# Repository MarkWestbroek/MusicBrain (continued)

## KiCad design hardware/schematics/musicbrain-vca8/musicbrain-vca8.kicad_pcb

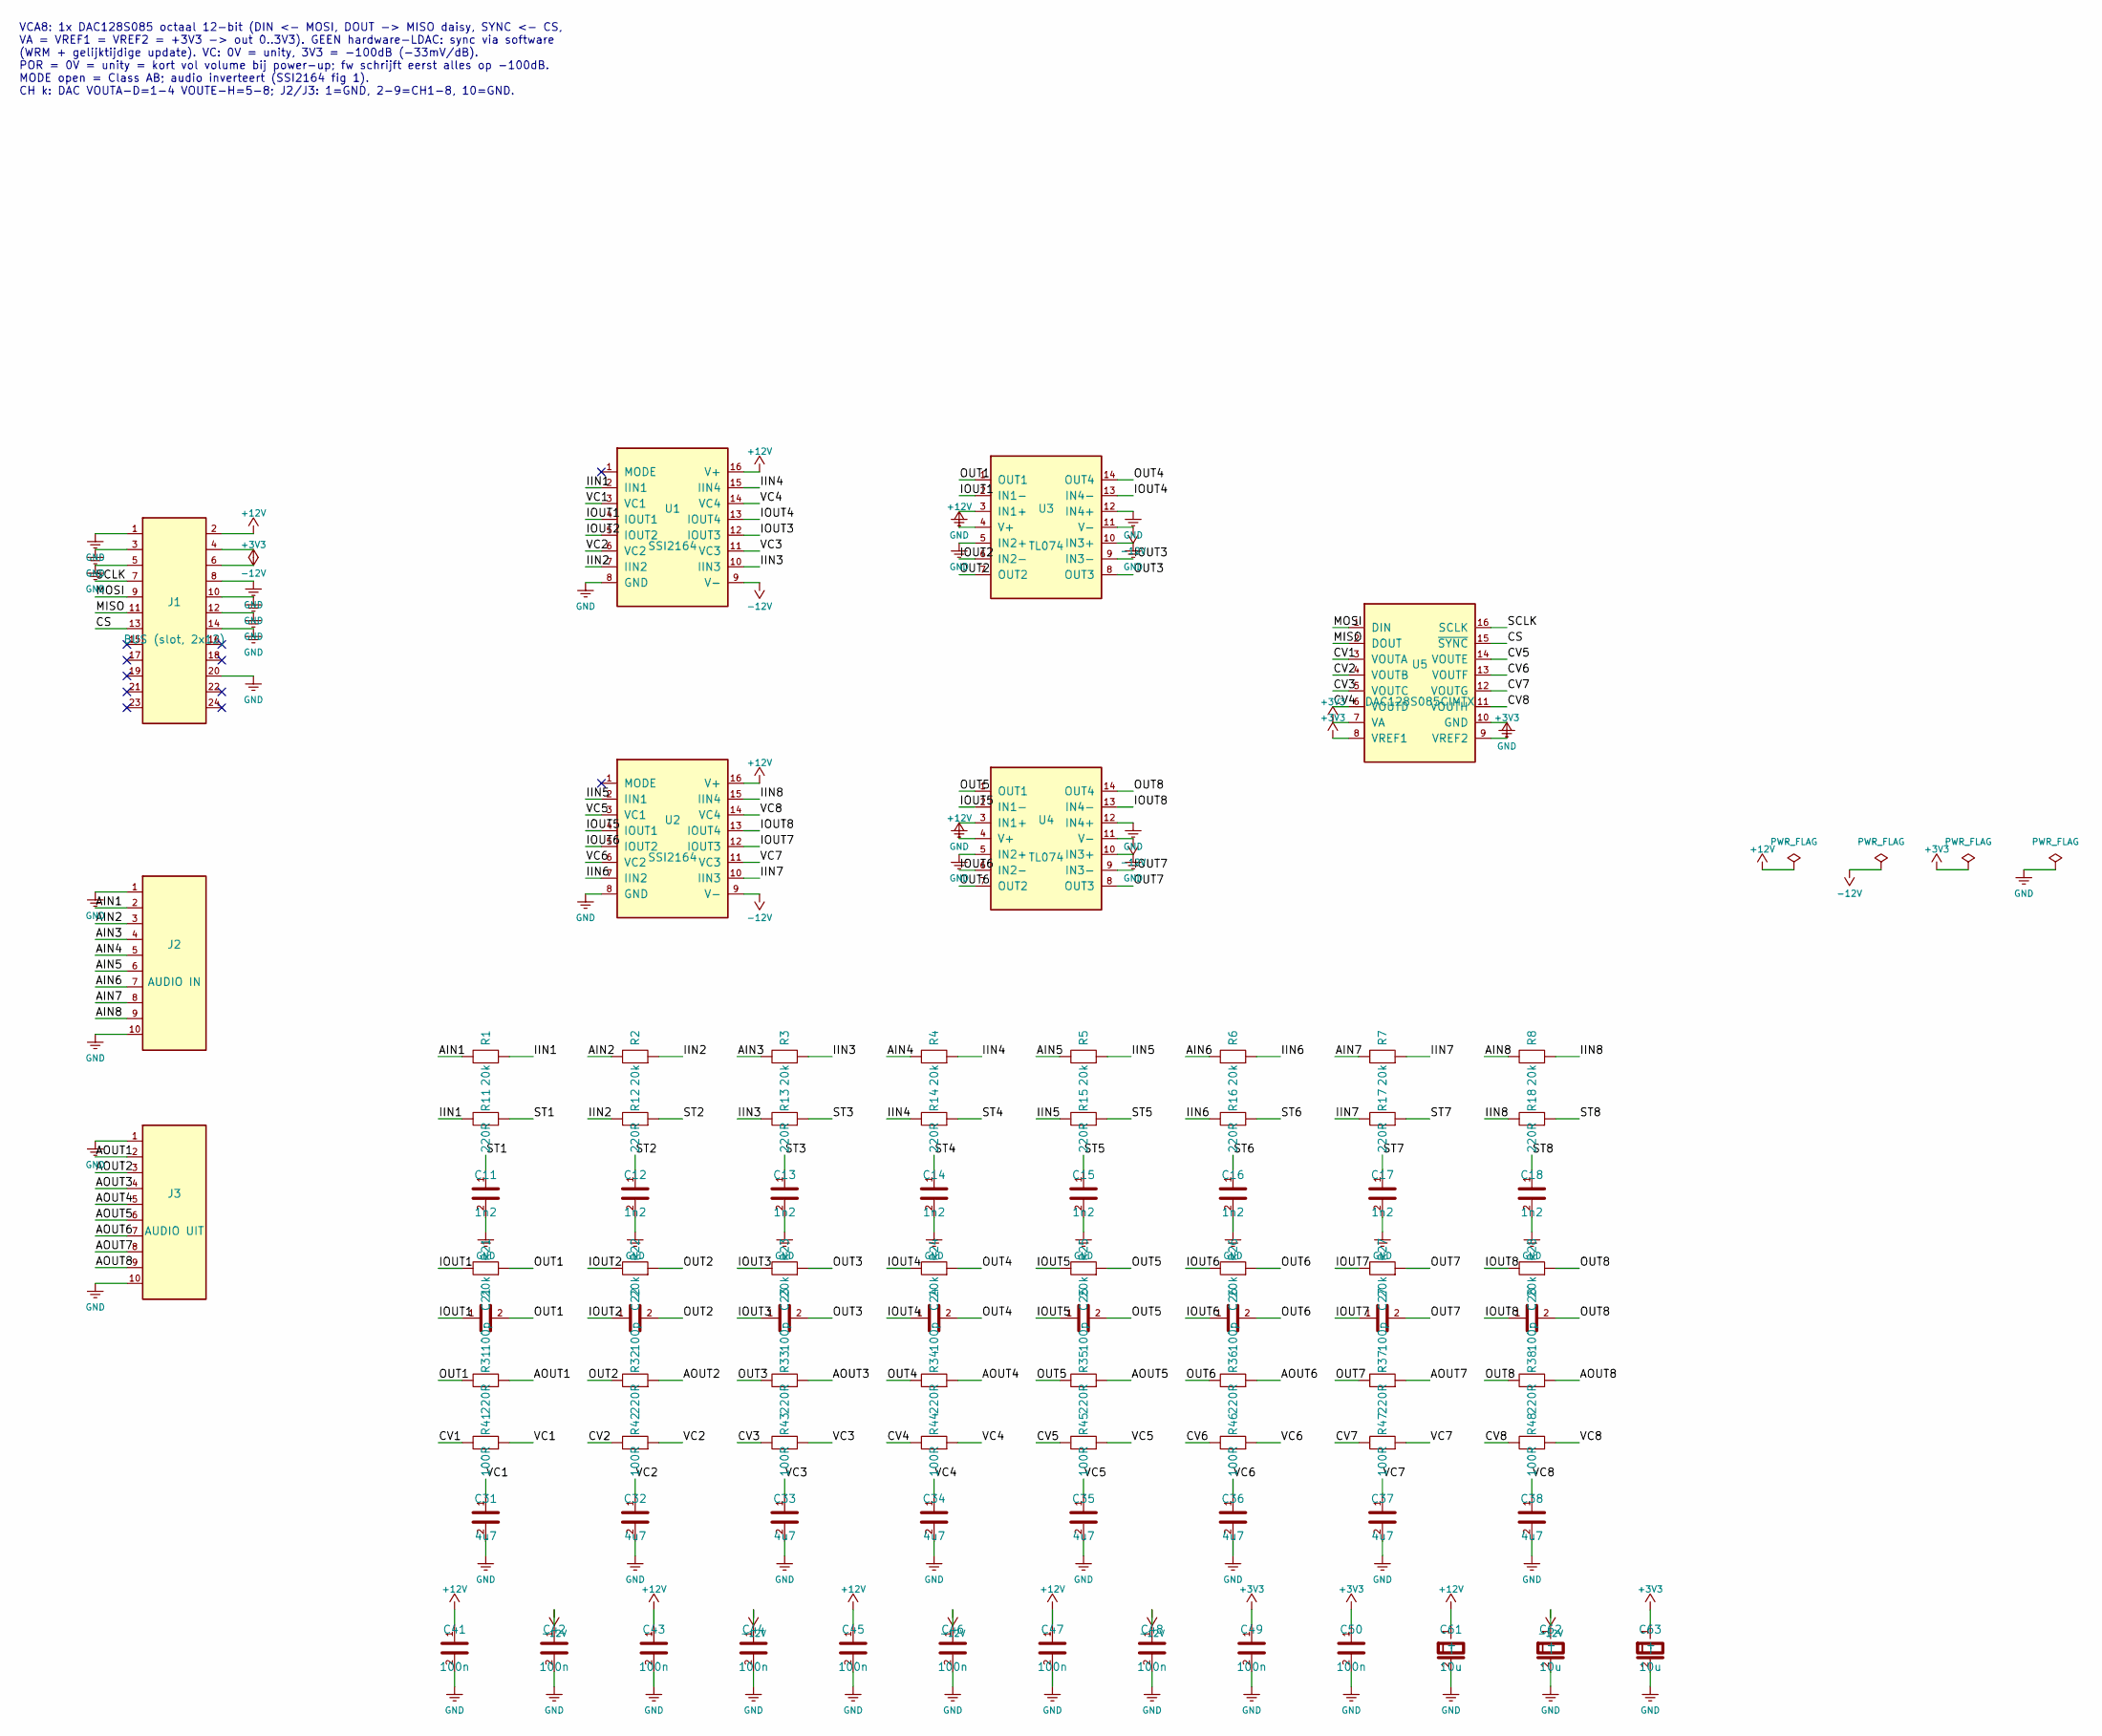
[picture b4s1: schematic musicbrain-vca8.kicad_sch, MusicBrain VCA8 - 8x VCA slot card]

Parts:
C11, C12, C13, C14, C15, C16, C17, C18: 1n2; C_0805_2012Metric
C21, C22, C23, C24, C25, C26, C27, C28: 100p; C_0805_2012Metric
C31, C32, C33, C34, C35, C36, C37, C38: 4u7; C_0805_2012Metric
C41, C42, C43, C44, C45, C46, C47, C48, C49, C50: 100n; C_0805_2012Metric
C61, C62, C63: 10u; CP_Elec_4x5.3
J1: BUS (slot, 2x12); PinHeader_2x12_P2.54mm_Horizontal
J2: AUDIO IN; PinHeader_1x10_P2.54mm_Horizontal
J3: AUDIO UIT; PinHeader_1x10_P2.54mm_Horizontal
R1, R2, R3, R4, R5, R6, R7, R8, R21, R22, R23, R24, R25, R26, R27, R28: 20k; R_0805_2012Metric
R11, R12, R13, R14, R15, R16, R17, R18, R31, R32, R33, R34, R35, R36, R37, R38: 220R; R_0805_2012Metric
R41, R42, R43, R44, R45, R46, R47, R48: 100R; R_0805_2012Metric
U1, U2: SSI2164; SOIC-16_3.9x9.9mm_P1.27mm
U3, U4: TL074; SOIC-14_3.9x8.7mm_P1.27mm
U5: DAC128S085CIMTX; TSSOP-16_4.4x5mm_P0.65mm

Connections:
+3V3: C49.1, C50.1, C63.1 (+), J1.6, U5.7 (VA), U5.8 (VREF1), U5.9 (VREF2)
+12V: C41.1, C43.1, C45.1, C47.1, C61.1 (+), J1.2, U1.16 (V+), U2.16 (V+), U3.4 (V+), U4.4 (V+)
-12V: C42.1, C44.1, C46.1, C48.1, C62.1 (+), J1.4, U1.9 (V-), U2.9 (V-), U3.11 (V-), U4.11 (V-)
/AIN1: J2.2, R1.1
/AIN2: J2.3, R2.1
/AIN3: J2.4, R3.1
/AIN4: J2.5, R4.1
/AIN5: J2.6, R5.1
/AIN6: J2.7, R6.1
/AIN7: J2.8, R7.1
/AIN8: J2.9, R8.1
/AOUT1: J3.2, R31.2
/AOUT2: J3.3, R32.2
/AOUT3: J3.4, R33.2
/AOUT4: J3.5, R34.2
/AOUT5: J3.6, R35.2
/AOUT6: J3.7, R36.2
/AOUT7: J3.8, R37.2
/AOUT8: J3.9, R38.2
/CS: J1.13, U5.15 (~SYNC)
/CV1: R41.1, U5.3 (VOUTA)
/CV2: R42.1, U5.4 (VOUTB)
/CV3: R43.1, U5.5 (VOUTC)
/CV4: R44.1, U5.6 (VOUTD)
/CV5: R45.1, U5.14 (VOUTE)
/CV6: R46.1, U5.13 (VOUTF)
/CV7: R47.1, U5.12 (VOUTG)
/CV8: R48.1, U5.11 (VOUTH)
/IIN1: R1.2, R11.1, U1.2 (IIN1)
/IIN2: R2.2, R12.1, U1.7 (IIN2)
/IIN3: R3.2, R13.1, U1.10 (IIN3)
/IIN4: R4.2, R14.1, U1.15 (IIN4)
/IIN5: R5.2, R15.1, U2.2 (IIN1)
/IIN6: R6.2, R16.1, U2.7 (IIN2)
/IIN7: R7.2, R17.1, U2.10 (IIN3)
/IIN8: R8.2, R18.1, U2.15 (IIN4)
/IOUT1: C21.1, R21.1, U1.4 (IOUT1), U3.2 (IN1-)
/IOUT2: C22.1, R22.1, U1.5 (IOUT2), U3.6 (IN2-)
/IOUT3: C23.1, R23.1, U1.12 (IOUT3), U3.9 (IN3-)
/IOUT4: C24.1, R24.1, U1.13 (IOUT4), U3.13 (IN4-)
/IOUT5: C25.1, R25.1, U2.4 (IOUT1), U4.2 (IN1-)
/IOUT6: C26.1, R26.1, U2.5 (IOUT2), U4.6 (IN2-)
/IOUT7: C27.1, R27.1, U2.12 (IOUT3), U4.9 (IN3-)
/IOUT8: C28.1, R28.1, U2.13 (IOUT4), U4.13 (IN4-)
/MISO: J1.11, U5.2 (DOUT)
/MOSI: J1.9, U5.1 (DIN)
/OUT1: C21.2, R21.2, R31.1, U3.1 (OUT1)
/OUT2: C22.2, R22.2, R32.1, U3.7 (OUT2)
/OUT3: C23.2, R23.2, R33.1, U3.8 (OUT3)
/OUT4: C24.2, R24.2, R34.1, U3.14 (OUT4)
/OUT5: C25.2, R25.2, R35.1, U4.1 (OUT1)
/OUT6: C26.2, R26.2, R36.1, U4.7 (OUT2)
/OUT7: C27.2, R27.2, R37.1, U4.8 (OUT3)
/OUT8: C28.2, R28.2, R38.1, U4.14 (OUT4)
/SCLK: J1.7, U5.16 (SCLK)
/ST1: C11.1, R11.2
/ST2: C12.1, R12.2
/ST3: C13.1, R13.2
/ST4: C14.1, R14.2
/ST5: C15.1, R15.2
/ST6: C16.1, R16.2
/ST7: C17.1, R17.2
/ST8: C18.1, R18.2
/VC1: C31.1, R41.2, U1.3 (VC1)
/VC2: C32.1, R42.2, U1.6 (VC2)
/VC3: C33.1, R43.2, U1.11 (VC3)
/VC4: C34.1, R44.2, U1.14 (VC4)
/VC5: C35.1, R45.2, U2.3 (VC1)
/VC6: C36.1, R46.2, U2.6 (VC2)
/VC7: C37.1, R47.2, U2.11 (VC3)
/VC8: C38.1, R48.2, U2.14 (VC4)
GND: C11.2, C12.2, C13.2, C14.2, C15.2, C16.2, C17.2, C18.2, C31.2, C32.2, C33.2, C34.2, C35.2, C36.2, C37.2, C38.2, C41.2, C42.2, C43.2, C44.2, C45.2, C46.2, C47.2, C48.2, C49.2, C50.2, C61.2 (-), C62.2 (-), C63.2 (-), J1.1, J1.3, J1.5, J1.8, J1.10, J1.12, J1.14, J1.20, J2.1, J2.10, J3.1, J3.10, U1.8 (GND), U2.8 (GND), U3.3 (IN1+), U3.5 (IN2+), U3.10 (IN3+), U3.12 (IN4+), U4.3 (IN1+), U4.5 (IN2+), U4.10 (IN3+), U4.12 (IN4+), U5.10 (GND)

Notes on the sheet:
VCA8: 1x DAC128S085 octaal 12-bit (DIN <- MOSI, DOUT -> MISO daisy, SYNC <- CS, VA = VREF1 = VREF2 = +3V3 -> out 0..3V3). GEEN hardware-LDAC: sync via software (WRM + gelijktijdige update). VC: 0V = unity, 3V3 = -100dB (-33mV/dB). POR = 0V = unity = kort vol volume bij power-up; fw schrijft eerst a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

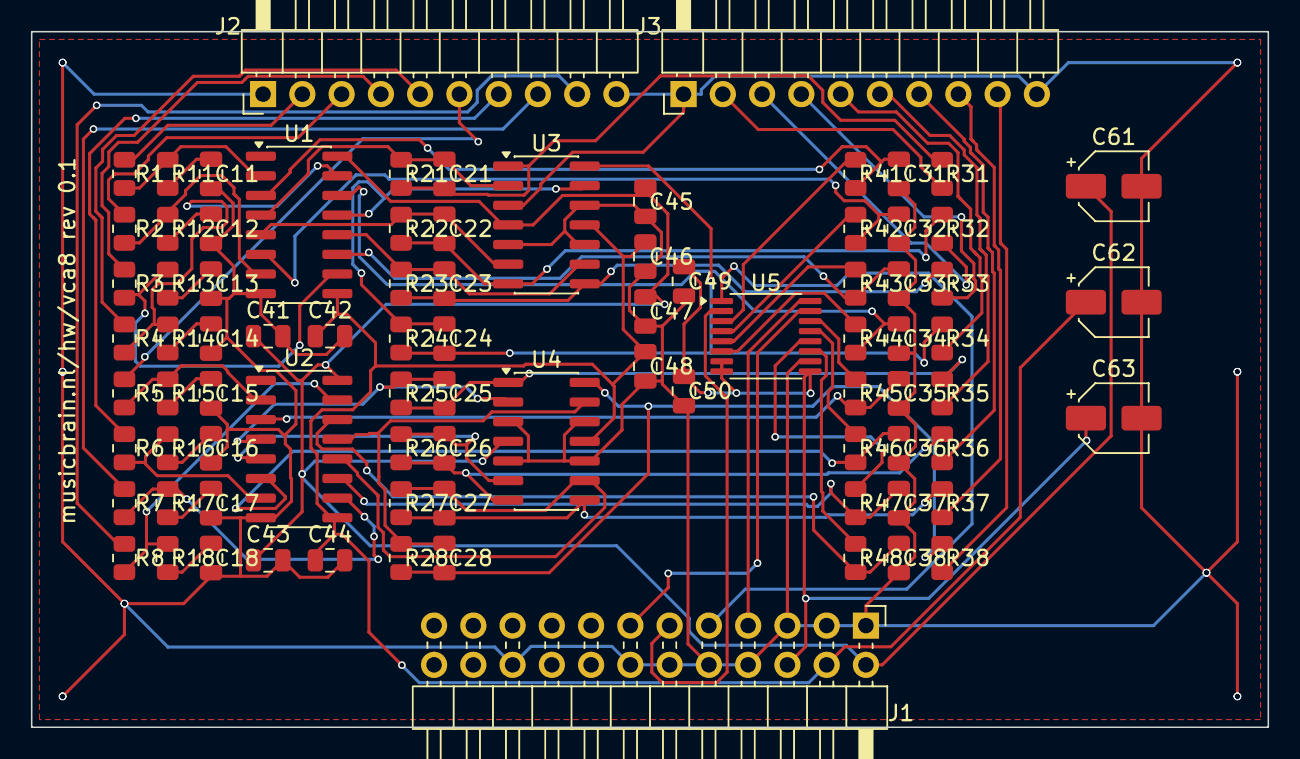
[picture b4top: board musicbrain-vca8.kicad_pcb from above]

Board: 2 copper layers, 80.0 x 45.0 mm, 85 parts (0 on the bottom side), 72 nets.

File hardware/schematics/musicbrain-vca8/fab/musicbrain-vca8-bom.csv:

"Comment","Designator","Footprint","LCSC Part #"
"1n2","C11,C12,C13,C14,C15,C16,C17,C18","C_0805_2012Metric","C2176739"
"100p","C21,C22,C23,C24,C25,C26,C27,C28","C_0805_2012Metric","C1790"
"4u7","C31,C32,C33,C34,C35,C36,C37,C38","C_0805_2012Metric","C1779"
"100n","C41,C42,C43,C44,C45,C46,C47,C48,C49,C50","C_0805_2012Metric","C49678"
"10u","C61,C62,C63","CP_Elec_4x5.3","C3343"
"BUS (slot, 2x12)","J1","PinHeader_2x12_P2.54mm_Horizontal","C2894992"
"AUDIO IN","J2","PinHeader_1x10_P2.54mm_Horizontal","C2687688"
"AUDIO UIT","J3","PinHeader_1x10_P2.54mm_Horizontal","C2687688"
"20k","R1,R2,R3,R4,R5,R6,R7,R8,R21,R22,R23,R24,R25,R26,R27,R28","R_0805_2012Metric","C4328"
"220R","R11,R12,R13,R14,R15,R16,R17,R18,R31,R32,R33,R34,R35,R36,R37,R38","R_0805_2012Metric","C17557"
"100R","R41,R42,R43,R44,R45,R46,R47,R48","R_0805_2012Metric","C17408"
"SSI2164","U1,U2","SOIC-16_3.9x9.9mm_P1.27mm",""
"TL074","U3,U4","SOIC-14_3.9x8.7mm_P1.27mm","C12594"
"DAC128S085CIMTX","U5","TSSOP-16_4.4x5mm_P0.65mm","C882851"

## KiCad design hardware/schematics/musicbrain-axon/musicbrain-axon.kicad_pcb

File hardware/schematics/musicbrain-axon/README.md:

# MusicBrain Axon — ESP32-S3-netbridge (rev 0.1)

**Praktisch:** de netwerkkaart van het Cortex-systeem. Een ESP32-S3 serveert
de editor-API over WiFi én bekabeld netwerk (W5500) en praat via één UART
met de master-Teensy op het busboard — zo krijgen patches en instellingen
het systeem in zonder USB-kabel. Plan: `doc/axon-plan.md`; ADR 0001/0002
beschrijven de sidecar-architectuur en de API (HTTP + WebSocket + mDNS).

**Status**: rev 0.1 AF — ERC 0, netcheck OK, **DRC 0/0** (freerouting met
protected handroutes voor USB/CC/LED; `--route-gnd`). Fab-pakket in `fab/`.
Nog niet besteld; eerst firmware-bring-up-plan.

## Aansluitoverzicht

## Blokken

- **U1 ESP32-S3-WROOM-1U** — de 1U met U.FL: antenne per kabel naar het
  paneel (metalen omgeving). Strapping IO0/IO3/IO45/IO46 vrijgehouden;
  BOOT+RESET-tactschakelaars.
- **U2 W5500** (SPI-Ethernet, LQFP48) op de ESP32-FSPI-pinnen
  (SCLK=IO12, MOSI=IO11, MISO=IO13, CS=IO10; INT=IO9, RST=IO14).
  Analoog front-end per WIZnet-referentie: 49R9-pull-ups op TXP/TXN,
  10R naar de TX-centertap, 6n8-seriecondensatoren in RX, 49R9+10n
  RX-terminatie, 22n op de RX-centertap, 12k4 EXRES, 25 MHz + 2×18p.
- **J3 MAGJACK (2×7)** — kabel naar een paneel-RJ45 mét geïntegreerde
  magnetics (HanRun HR911105A-klasse). **Kabel kort houden (<15 cm) en de
  TX/RX-paren bij elkaar**; shield via 1n/2kV + 1M aan GND.
- **J1 BUSBOARD (1×6)** — twee **rechte 1:1-kabeltjes** naar het busboard.
  Pin-volgorde bewust zó dat er niets gekruist hoeft (de UART-TX↔RX-wissel
  zit al in de pinvolgorde):

  | J1 | signaal | → busboard | kabel |
  |----|---------|-----------|-------|
  | 1  | +5V     | J25.1 +5V | power (2 draden) |
  | 2  | GND     | J25.2 GND | power |
  | 3  | GND     | J19.1 GND | UART (4 draden) |
  | 4  | RX (AXON_RX) | J19.2 DLG1_TX | UART |
  | 5  | TX (AXON_TX) | J19.3 DLG1_RX | UART |
  | 6  | GND     | J19.4 GND | UART |

  Op busboard rev 3.2 kan dezelfde 1×6 rechtstreeks in een verticale socket.

  > ⚠️ **Oriëntatie bij assemblage**: enkelrijige headers keyen niet. De
  > **2-pin (+5V/GND)** omgekeerd = voeding omgepoold (schade). De **4-pin**
  > lijkt symmetrisch (GND aan beide kanten) maar omgedraaid wisselen RX↔TX.
  > Pin 1 (silk "5V") van elke kabel markeren. Bij de directe koppeling op
  > busboard 3.2 (geen kabel): kale header, in de bouwinstructie vastleggen
  > dat connectoren/componenten naar binnen wijzen (shroud = terugval) — zie
  > `doc/axon-plan.md`.
- **J2 USB-C** — alleen eerste flash/debug; VBUS voedt het bord via een
  SS34 (bus-5V wint als beide aangesloten zijn). Daarna gaat firmware
  via WiFi-OTA.
- **U3 AMS1117-3.3** + ferriet naar de analoge 3V3 van de W5500.
- **J4 DEBUG (1×3)**: UART0 TX/RX/GND.

## Firmware-kant (nog te bouwen)

Zelfde JSON-RPC-frames als over USB-CDC (ADR 0002): de Teensy ziet een
`Transport` op Serial3; de ESP32 termineert HTTP/WebSocket/mDNS
(`musicbrain.local`) en straks OTA. Recepten uit het gswitch-project
(ESP32-S3, WiFi-OTA, USB-flash) zijn herbruikbaar.

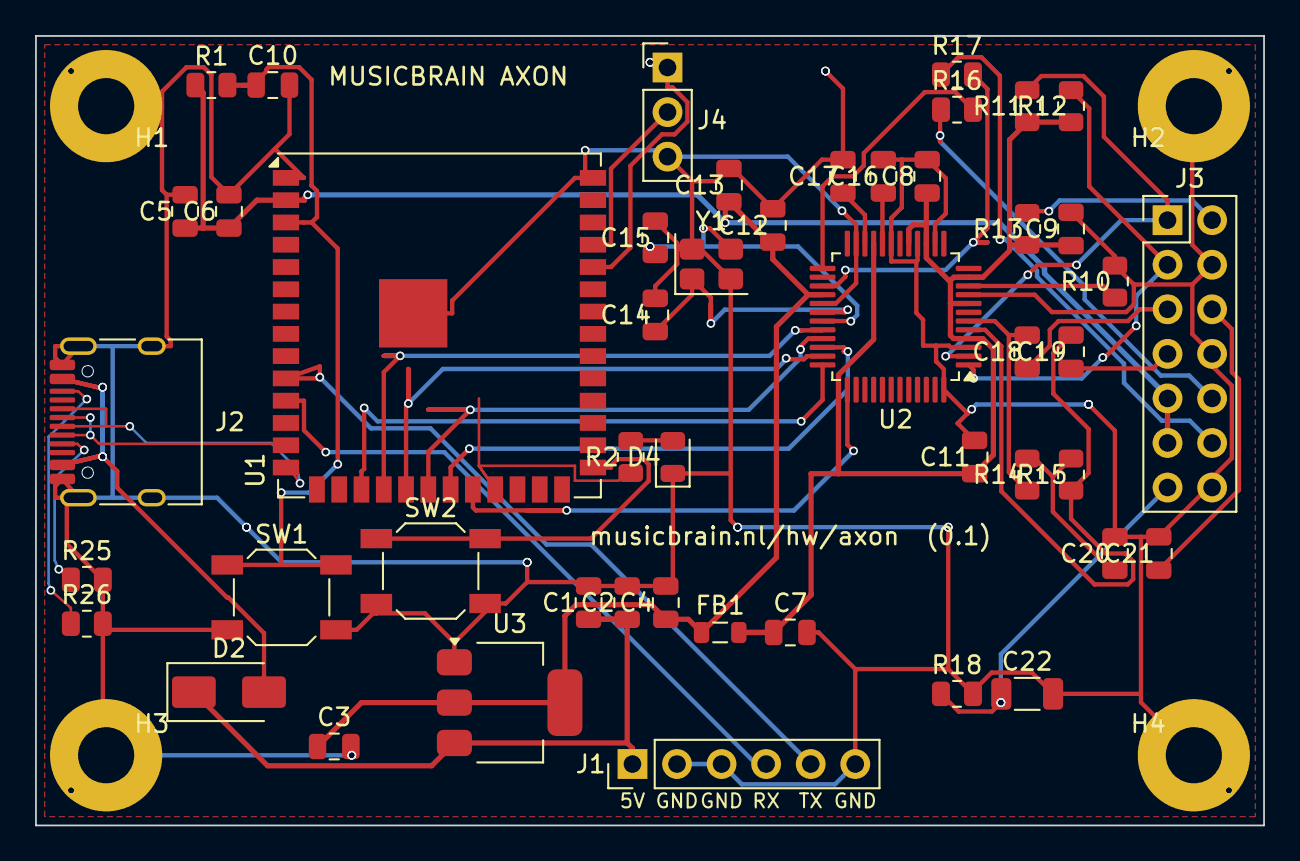
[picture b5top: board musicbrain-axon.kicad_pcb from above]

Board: 2 copper layers, 70.0 x 45.0 mm, 52 parts (0 on the bottom side), 42 nets.

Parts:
C1, C3, C5: 22u; C_0805_2012Metric
C2, C4, C6, C8, C9, C11, C12: 100n; C_0805_2012Metric
C7, C13: 10u; C_0805_2012Metric
C10: 1u; C_0805_2012Metric
C14, C15: 18p; C_0805_2012Metric
C16: 4u7; C_0805_2012Metric
C17, C20: 10n; C_0805_2012Metric
C18, C19: 6n8; C_0805_2012Metric
C21: 22n; C_0805_2012Metric
C22: 1n-2kV; C_1206_3216Metric
D2: SS34; D_SMA
D4: LED-GN; LED_0805_2012Metric
FB1: FB121; L_0805_2012Metric
H1, H2, H3, H4: M3; MountingHole_3.2mm_M3_Pad
J1: BUSBOARD; PinHeader_1x06_P2.54mm_Vertical
J2: USB-C; USB_C_Receptacle_HRO_TYPE-C-31-M-12
J3: MAGJACK; PinHeader_2x07_P2.54mm_Vertical
J4: DEBUG; PinHeader_1x03_P2.54mm_Vertical
R1: 10k; R_0805_2012Metric
R2: 1k; R_0805_2012Metric
R10: 12k4; R_0805_2012Metric
R11, R12, R14, R15: 49R9; R_0805_2012Metric
R13: 10R; R_0805_2012Metric
R16, R17: 330R; R_0805_2012Metric
R18: 1M; R_0805_2012Metric
R25, R26: 5k1; R_0805_2012Metric
SW1: RESET; SW_SPST_SKQG_WithStem
SW2: BOOT; SW_SPST_SKQG_WithStem
U1: ESP32-S3-WROOM-1U-N8R2; ESP32-S3-WROOM-1U
U2: W5500; LQFP-48_7x7mm_P0.5mm
U3: AMS1117-3.3; SOT-223-3_TabPin2
Y1: 25MHz; Crystal_SMD_3225-4Pin_3.2x2.5mm

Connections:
+3V3: C3.1, C4.1, C5.1, C6.1, C12.1, C13.1, FB1.1, J3.9, J3.11, R1.1, U1.2, U2.28, U3.2
+3V3A: C7.1, C8.1, C9.1, C11.1, FB1.2, R11.1, R12.1, R13.1, U2.4, U2.8, U2.11, U2.15, U2.17, U2.21
+5V: C1.1, C2.1, D2.1, J1.1, U3.3
/ACTLED: R17.2, U2.27
/ACT_K: J3.12, R17.1
/AXON_RX: J1.4, U1.11
/AXON_TX: J1.5, U1.10
/BOOT: SW2.1, U1.27
/CC1: J2.A5, R25.1
/CC2: J2.B5, R26.1
/DBG_RX: J4.2, U1.37
/DBG_TX: J4.1, U1.36
/ESP_EN: C10.1, R1.2, SW1.1, U1.3
/EXRES: R10.1, U2.10
/LEDK: D4.2, R2.2
/LEDK_A: R2.1, U1.23
/LINKLED: R16.2, U2.25
/LINK_K: J3.10, R16.1
/RCT: C21.1, J3.6
/RD_N: C19.1, J3.7
/RD_P: C18.1, J3.5
/RXN: C19.2, R15.1, U2.5
/RXP: C18.2, R14.1, U2.6
/RXTRM: C20.1, R14.2, R15.2
/SHLD: C22.1, J3.13, R18.1
/TCT: J3.2, R13.2
/TOCAP: C16.1, U2.20
/TXN: J3.3, R12.2, U2.1
/TXP: J3.1, R11.2, U2.2
/USB_DM: J2.A7, J2.B7, U1.13
/USB_DP: J2.A6, J2.B6, U1.14
/V12O: C17.1, U2.22
/VBUS: D2.2, J2.A4, J2.A9, J2.B4, J2.B9
/W_CS: U1.18, U2.32
/W_INT: U1.17, U2.36
/W_MISO: U1.21, U2.34
/W_MOSI: U1.19, U2.35
/W_RST: U1.22, U2.37
/W_SCLK: U1.20, U2.33
/XI: C14.1, U2.30, Y1.1
/XO: C15.1, U2.31, Y1.3
GND: C1.2, C2.2, C3.2, C4.2, C5.2, C6.2, C7.2, C8.2, C9.2, C10.2, C11.2, C12.2, C13.2, C14.2, C15.2, C16.2, C17.2, C20.2, C21.2, C22.2, D4.1, H1.1, H2.1, H3.1, H4.1, J1.2, J1.3, J1.6, J2.A1, J2.A12, J2.B1, J2.B12, J2.SH, J3.4, J3.8, J3.14, J4.3, R10.2, R18.2, R25.2, R26.2, SW1.2, SW2.2, U1.1, U1.40, U1.41, U2.3, U2.9, U2.14, U2.16, U2.19, U2.23, U2.29, U2.48, U3.1, Y1.2, Y1.4

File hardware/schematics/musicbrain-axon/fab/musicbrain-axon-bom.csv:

"Comment","Designator","Footprint","LCSC Part #"
"22u","C1,C3,C5","C_0805_2012Metric",""
"100n","C2,C4,C6,C8,C9,C11,C12","C_0805_2012Metric","C49678"
"10u","C7,C13","C_0805_2012Metric","C440198"
"1u","C10","C_0805_2012Metric","C5137478"
"18p","C14,C15","C_0805_2012Metric",""
"4u7","C16","C_0805_2012Metric",""
"10n","C17,C20","C_0805_2012Metric",""
"6n8","C18,C19","C_0805_2012Metric",""
"22n","C21","C_0805_2012Metric",""
"1n-2kV","C22","C_1206_3216Metric",""
"DIODE","D2","D_SMA",""
"LED","D4","LED_0805_2012Metric",""
"FERRIET","FB1","L_0805_2012Metric",""
"M3","H1,H2,H3,H4","MountingHole_3.2mm_M3_Pad",""
"BUSBOARD (J25+J19)","J1","PinHeader_1x06_P2.54mm_Vertical",""
"USBC16","J2","USB_C_Receptacle_HRO_TYPE-C-31-M-12",""
"MAGJACK (paneel)","J3","PinHeader_2x07_P2.54mm_Vertical",""
"DEBUG","J4","PinHeader_1x03_P2.54mm_Vertical",""
"10k","R1","R_0805_2012Metric","C17414"
"1k","R2","R_0805_2012Metric","C17513"
"12k4","R10","R_0805_2012Metric",""
"49R9","R11,R12,R14,R15","R_0805_2012Metric",""
"10R","R13","R_0805_2012Metric","C17415"
"330R","R16,R17","R_0805_2012Metric",""
"1M","R18","R_0805_2012Metric",""
"5k1","R25,R26","R_0805_2012Metric",""
"SW_TACT","SW1,SW2","SW_SPST_SKQG_WithStem",""
"ESP32-S3-WROOM-1U","U1","ESP32-S3-WROOM-1U",""
"W5500","U2","LQFP-48_7x7mm_P0.5mm",""
"AMS1117-33","U3","SOT-223-3_TabPin2",""
"XTAL4","Y1","Crystal_SMD_3225-4Pin_3.2x2.5mm",""
